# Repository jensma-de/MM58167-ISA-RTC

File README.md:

# MM58167-ISA-RTC

## What is this?
A 8bit real time clock for old computers. Keeps the time when the computer is shut down. Fully covered address bus to prevent conflicts.
The backup battery should theoretically last for about six years.

## Why is this?
Yes, there are many more modern RTC's out there. I made this just for fun and with parts that were readily available back in the 80s. I like to keep things period correct 😉

## How to use it?
First set the jumpers for the RTC. You can choose between 200h, 240h, 300h and 340h.

Plug the card into a free ISA slot, either 8bit or 16bit.

Download the control prgram and put it on your PC:

Control program:
[MM58167.EXE](./prog/MM58167.EXE) (Source: [MM58167.BAS](./prog/MM58167.BAS))

Alternative German version:

Control program: [MM58167_GER.EXE](./prog/MM58167_GER.EXE) (Source: [MM58167_GER.BAS](./prog/MM58167_GER.BAS))

Next, have a look at the usage description:
```
Usage:
------

MM58167.EXE ADDRESSh SET|GET [VERBOSE] [FORCE] [NOEX]

Adressh:   The address of the RTC, set by jumpers on the PCB, e.g. 240h
SET|GET:   Sets the RTC to the system clock and vise versa.
[VERBOSE]: Outputs some information.
[FORCE]:   Force given address without checking for plausible RTC data.
[NOEX]:    Don't export the time to C:\MM581.RTC.
           The file is needed to update the year automatically.

Example:
To write the system time to the RTC, setup at 300h:
MM58167.EXE 300h SET

--------------------------------------------------------
Credits to:
github.com/mrehkopf/ & github.com/Sciurus68k/

Project page:
github.com/jensma-de/MM58167-ISA-RTC/
```

At first you need to set the current time and date to the clock:
```
date
```

After this command you can set the date interactively. Next up is the time:

```
time
```

Same interactive configuration here. Next up you put your time and date into the RTC (assuming you configured it for adress 340h):

```
MM58167.EXE 340h SET
```

Now the RTC is set and should, if you put in a CR2032 coin cell into it, keep the time.

To read the date and time from the RTC to update your system on startup, add this to your C:\AUTOSTART.BAT:

```
MM58167.EXE 340h GET
```

That's it!

Only if you're having problems with the interrupt output: cut the trace between the two pads of the jumper in the top left corner of the pcb. Then close the center and the right pad.

## Is this Y2K-compatible?
Yes. Just make sure your OS can handle dates after 1999!

## I've heard the MM58167 is terribly old and can't even increment years by it's own
That's right. In order increment the year automatically the MM58167.EXE offloads some information to C:\MM581.RTC.
If you don't want this for some reason you can disable it with the NOEX argument.

Downside to all of this is that you have to start your computer at least once in two years. But seriously - if you boot up your PC that rarely you might want to remove the time keeping battery anyways :)

## BOM

**Note for the battery holder**: The holder I used is just labeled "Rainpro". No idea about the exact model. Should be a very common CR2032 battery holder, though. Here's a picture of the listing:

Alternatively you can download and check out the interactive BOM:
[iBOM](./info/ibom.html)

## Pictures and schematics
[Schematics](./info/schematics.pdf)

[Photo of assembled RTC](./info/assembled.jpg)

## Credit
[@mrehkopf](https://github.com/mrehkopf)
[@Sciurus68k](https://github.com/Sciurus68k)

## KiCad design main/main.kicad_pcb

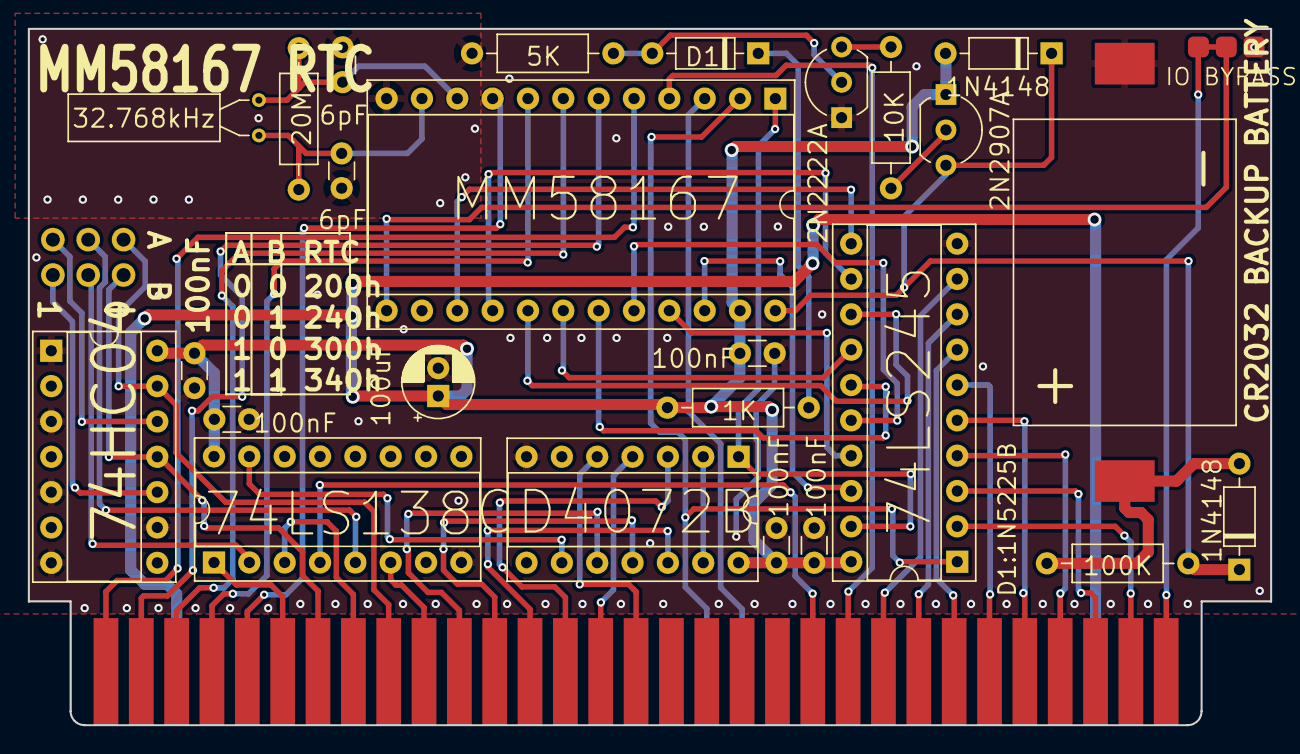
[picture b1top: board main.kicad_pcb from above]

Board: 2 copper layers, 89.3 x 50.0 mm, 29 parts (0 on the bottom side), 54 nets.

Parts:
BT1: Battery; Rainpro CR2032
BUS1: Bus_ISA_8bit; BUS_AT
C1, C2: 6pF; C_Disc_D3.0mm_W1.6mm_P2.50mm
C3: 100uF; CP_Radial_D5.0mm_P2.00mm
C4, C5, C6, C7, C8: 100nF; C_Disc_D3.0mm_W1.6mm_P2.50mm
D1, D2: 1N4148; D_DO-35_SOD27_P7.62mm_Horizontal
D3: 1N5225B; D_DO-35_SOD27_P7.62mm_Horizontal
JP1, JP2: Jumper_3_Open; PinHeader_1x03_P2.54mm_Vertical
JP3: Jumper_3_Bridged12; jumper_3
Q1: 2N2907A; TO-92_Inline_Wide
Q2: 2N2222A; TO-92_Inline_Wide
R1: 20M; R_Axial_DIN0207_L6.3mm_D2.5mm_P10.16mm_Horizontal
R2: 100K; R_Axial_DIN0207_L6.3mm_D2.5mm_P10.16mm_Horizontal
R3: 10K; R_Axial_DIN0207_L6.3mm_D2.5mm_P10.16mm_Horizontal
R4: 1K; R_Axial_DIN0207_L6.3mm_D2.5mm_P10.16mm_Horizontal
R5: 5K; R_Axial_DIN0207_L6.3mm_D2.5mm_P10.16mm_Horizontal
U1: 74LS245; DIP-20_W7.62mm_Socket
U2: 74LS138; DIP-16_W7.62mm_Socket
U3: 74HC04; DIP-14_W7.62mm_Socket
U4: MM58167; DIP-24_W15.24mm_Socket
U6: 4072; DIP-14_W7.62mm_Socket
Y1: 32.768kHz; Crystal_AT310_D3.0mm_L10.0mm_Horizontal

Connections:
/A0: BUS1.62 (BA00), U4.5 (A0)
/A1: BUS1.61 (BA01), U4.6 (A1)
/A2: BUS1.60 (BA02), U4.7 (A2)
/A3: BUS1.59 (BA03), U4.8 (A3)
/A4: BUS1.58 (BA04), U4.9 (A4)
/A5: BUS1.57 (BA05), U2.1 (A0)
/A7: BUS1.55 (BA07), U2.3 (A2)
/A9: BUS1.53 (BA09), U2.6 (E3)
/A10: BUS1.52 (BA10), U6.10
/A11: BUS1.51 (BA11), U6.11
/A12: BUS1.50 (BA12), U6.12
/A13: BUS1.49 (BA13), U6.3
/A14: BUS1.48 (BA14), U6.4
/A15: BUS1.47 (BA15), U6.5
/D0: BUS1.40 (DB0), U1.9 (A7)
/D1: BUS1.39 (DB1), U1.8 (A6)
/D2: BUS1.38 (DB2), U1.7 (A5)
/D3: BUS1.37 (DB3), U1.6 (A4)
/D4: BUS1.36 (DB4), U1.5 (A3)
/D5: BUS1.35 (DB5), U1.4 (A2)
/D6: BUS1.34 (DB6), U1.3 (A1)
/D7: BUS1.33 (DB7), U1.2 (A0)
/DB0: U1.11 (B7), U4.15 (D0)
/DB1: U1.12 (B6), U4.16 (D1)
/DB2: U1.13 (B5), U4.17 (D2)
/DB3: U1.14 (B4), U4.18 (D3)
/DB4: U1.15 (B3), U4.19 (D4)
/DB5: U1.16 (B2), U4.20 (D5)
/DB6: U1.17 (B1), U4.21 (D6)
/DB7: U1.18 (B0), U4.22 (D7)
A6_IN: BUS1.56 (BA06), JP2.1 (A), U3.11
A6_OUT: JP2.2 (C), U2.2 (A1)
A8_IN: BUS1.54 (BA08), JP1.1 (A), U3.13
A8_OUT: JP1.2 (C), U2.5 (E2)
AEN: BUS1.42 (AEN), U2.4 (E1)
GND: BT1.2 (-), BUS1.1 (GND), BUS1.10 (GND), BUS1.31 (GND), C1.2, C2.2, C3.2, C4.2, C5.2, C6.2, C7.2, C8.2, JP3.3 (B), Q2.1 (E), R5.1, U1.10 (GND), U2.8 (GND), U3.1, U3.3, U3.5, U3.7 (GND), U3.9, U4.12 (VSS), U6.7 (VSS)
IO: BUS1.32 (IO), JP3.1 (A), JP3.2 (C), U4.13 (INTERRUPT_OUT)
IOR: BUS1.14 (~IOR), U1.1 (A->B), U4.2 (/RD)
IORDY: BUS1.41 (IO_READY), U4.4 (/RDY)
IOW: BUS1.13 (~IOW), U4.3 (/WR)
unnamed: BT1.1 (+), D1.2 (A), R2.2
unnamed: D1.1 (K), D2.1 (K), Q1.3 (C), R2.1, U4.24 (VDD)
unnamed: D3.2 (A), Q2.2 (B), R5.2
unnamed: D3.1 (K), R4.1
unnamed: JP1.3 (B), U3.12
unnamed: JP2.3 (B), U3.10
unnamed: Q1.2 (B), R3.2
unnamed: Q2.3 (C), R3.1
unnamed: U1.19 (CE), U4.1 (/CS), U6.1
unnamed: U2.15 (O0), U6.9
unnamed: C1.1, R1.1, U4.10 (OSC_IN), Y1.1
unnamed: C2.1, R1.2, U4.11 (OSC_OUT), Y1.2
unnamed: U6.2, U6.13
VCC: BUS1.3 (VCC), BUS1.29 (VCC), C3.1, C4.1, C5.1, C6.1, C7.1, C8.1, D2.2 (A), Q1.1 (E), R4.2, U1.20 (VCC), U2.16 (VCC), U3.14 (VCC), U4.23 (/PWR_DOWN), U6.14 (VDD)

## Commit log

2022-10-25 init
2022-10-30 Add files via upload
    interactivehtmlbom
2022-10-30 init
    init
